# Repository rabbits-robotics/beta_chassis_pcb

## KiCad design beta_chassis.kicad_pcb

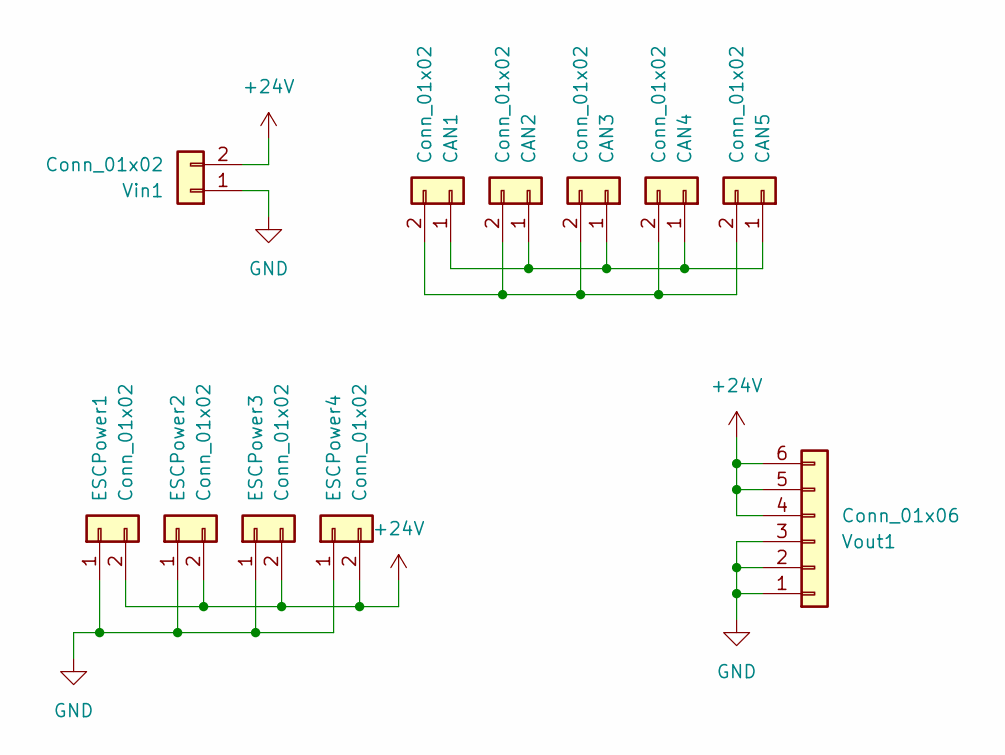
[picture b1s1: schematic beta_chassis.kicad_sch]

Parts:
CAN1, CAN2, CAN3, CAN4, CAN5: Conn_01x02; JST_PH_B2B-PH-K_1x02_P2.00mm_Vertical
ESCPower1, ESCPower2, ESCPower3, ESCPower4: Conn_01x02; AMASS_XT30U-F_1x02_P5.0mm_Vertical
Vin1: Conn_01x02; AMASS_XT30U-M_1x02_P5.0mm_Vertical
Vout1: Conn_01x06; JST_PH_B6B-PH-K_1x06_P2.00mm_Vertical

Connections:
+24V: ESCPower1.2, ESCPower2.2, ESCPower3.2, ESCPower4.2, Vin1.2, Vout1.4, Vout1.5, Vout1.6
GND: ESCPower1.1, ESCPower2.1, ESCPower3.1, ESCPower4.1, Vin1.1, Vout1.1, Vout1.2, Vout1.3
unnamed: CAN1.1, CAN2.1, CAN3.1, CAN4.1, CAN5.1
unnamed: CAN1.2, CAN2.2, CAN3.2, CAN4.2, CAN5.2

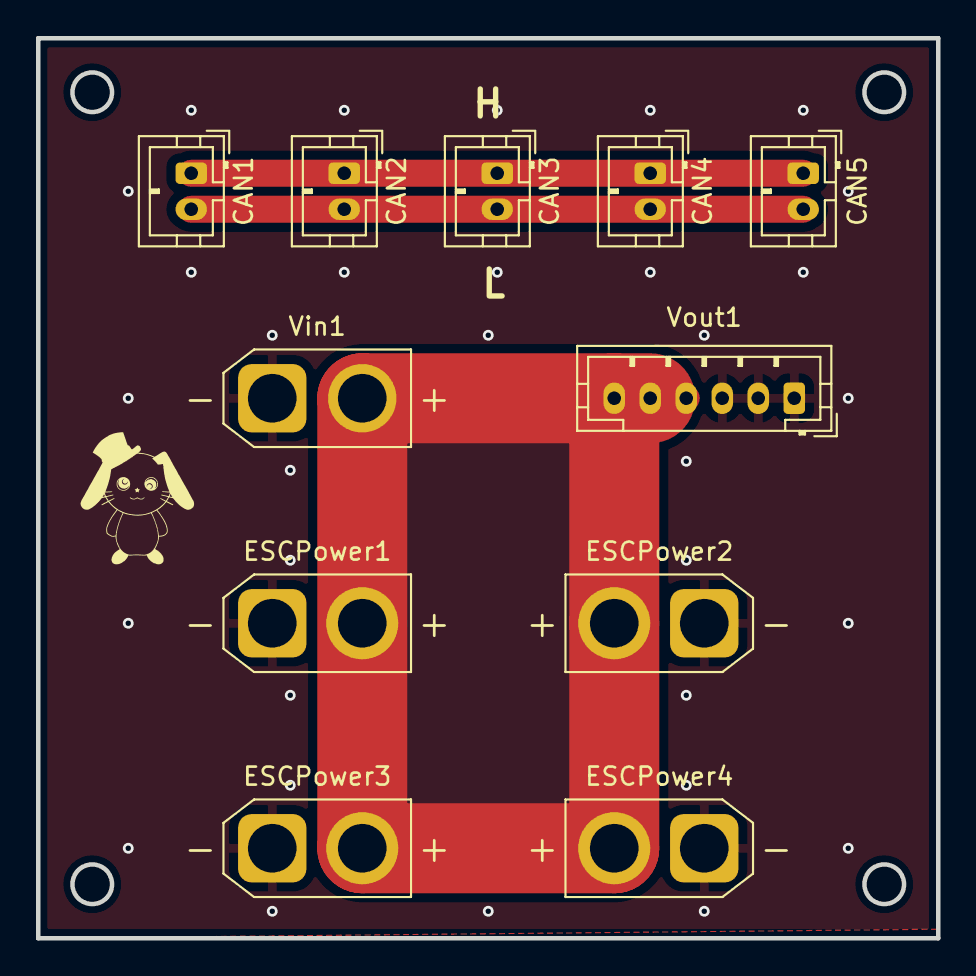
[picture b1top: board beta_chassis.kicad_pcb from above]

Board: 2 copper layers, 50.0 x 50.0 mm, 11 parts (0 on the bottom side), 4 nets.

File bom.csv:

"Reference","Value","Footprint","QUANTITY"
"CAN1-CAN5","Conn_01x02","Connector_JST:JST_PH_B2B-PH-K_1x02_P2.00mm_Vertical","5"
"ESCPower1-ESCPower4","Conn_01x02","Connector_AMASS:AMASS_XT30U-F_1x02_P5.0mm_Vertical","4"
"Vin1","Conn_01x02","Connector_AMASS:AMASS_XT30U-M_1x02_P5.0mm_Vertical","1"
"Vout1","Conn_01x06","Connector_JST:JST_PH_B6B-PH-K_1x06_P2.00mm_Vertical","1"
